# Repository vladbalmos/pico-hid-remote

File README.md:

## HID Bluetooth Remote

HID Bluetooth (BLE) Remote based on a Pico W.

## Hardware requirements

* Pico W
* 5 x micro switches
* TP5100 charging module
* micro USB female
* 1 x 18650 lithium battery (for the V1 enclosure)
* 1 x blackberry q10 lithium battery (for the V2 enclosure)
* 1 x 3mm blue LED + 10k resistor
* 3 x 3mm green LED + 3 x 1k resistors
* 2 x 100k resistors
* pico probe (optional)

## Software dependencies

* pico-sdk (1.5.0)
* pico-extras
* opencd (optional)
* pico probe (optional)

## Build

    make build
    
## Install
Via pico probe:

    make install

## Buttons

* FN
    - long press - turn off
    - double press - show baterry level
    
* PLAY
    - wakeup from sleep if sleeping
    - toggle play/pause
    
* VOL UP
    - increase volume

* VOL DOWN
    - decrease volume

* RESET
    - reset PICO
    
## Behaviour
    
On startup the device is discoverable for one minute, after which, if not paired, the device will go to sleep to preserve battery.

If the device is paired, discoverability is turned off until disconnected.

Once paired, the device will go to sleep if no button press was detected in 10 minutes in order to preserve battery.

### LEDs

* blue
    - flashes while not connected and in pairing mode
    - off once paired
    
* 3 x green
    - show battery level
    - if battery level <= 5% the last led in will flash for 5 seconds

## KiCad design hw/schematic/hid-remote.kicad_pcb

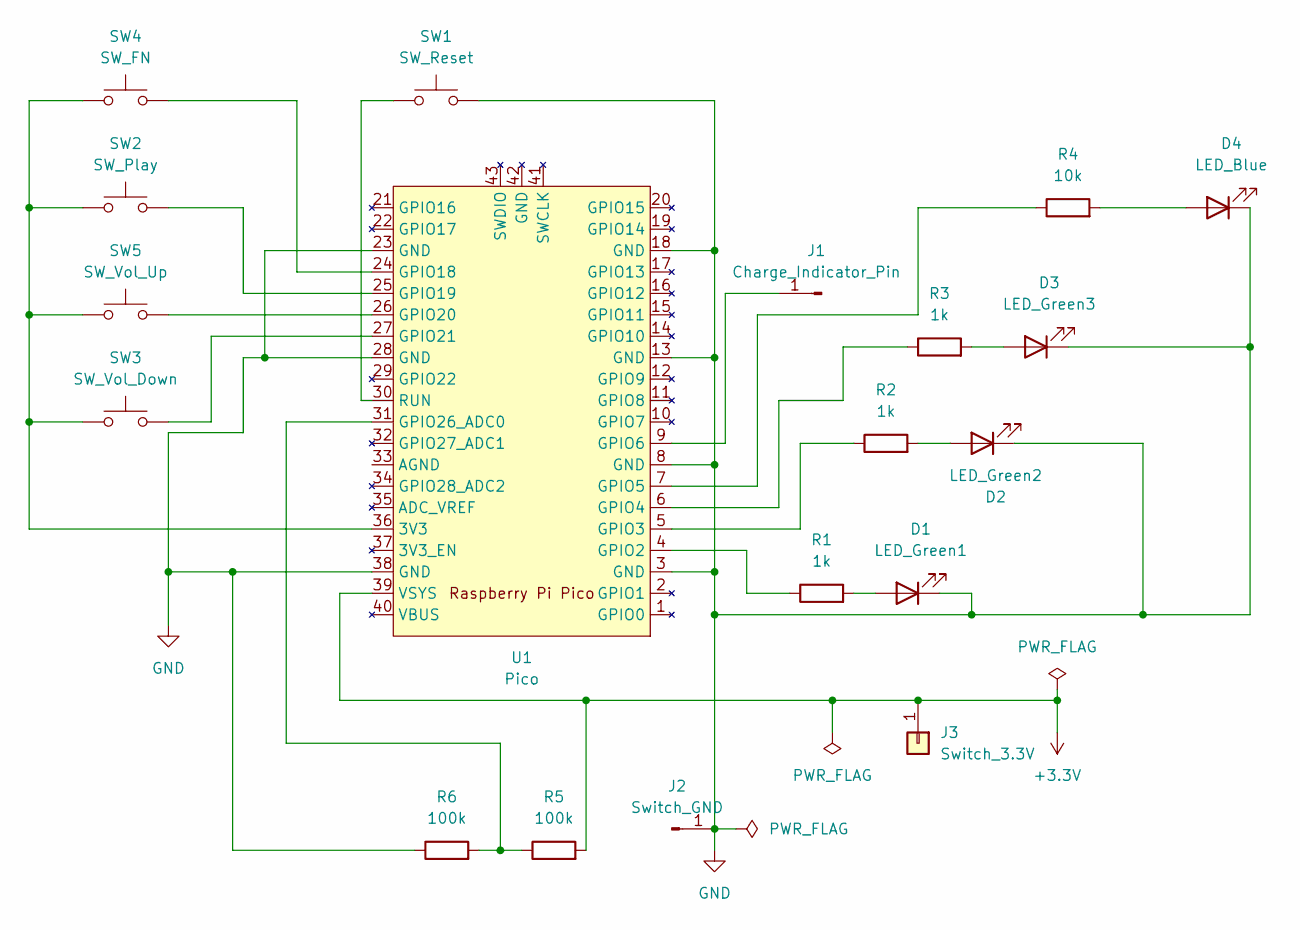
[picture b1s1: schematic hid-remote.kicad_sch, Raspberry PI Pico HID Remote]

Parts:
D1: LED_Green1; LED_0201_0603Metric_Pad0.64x0.40mm_HandSolder
D2: LED_Green2; LED_0201_0603Metric_Pad0.64x0.40mm_HandSolder
D3: LED_Green3; LED_0201_0603Metric_Pad0.64x0.40mm_HandSolder
D4: LED_Blue; LED_0201_0603Metric_Pad0.64x0.40mm_HandSolder
J1: Charge_Indicator_Pin; PinSocket_1x01_P2.54mm_Vertical
J2: Switch_GND; PinSocket_1x01_P2.54mm_Vertical
J3: Switch_3.3V; PinSocket_1x01_P2.54mm_Vertical
R1, R2, R3: 1k; R_Axial_DIN0204_L3.6mm_D1.6mm_P5.08mm_Horizontal
R4: 10k; R_Axial_DIN0207_L6.3mm_D2.5mm_P10.16mm_Horizontal
R5, R6: 100k; R_Axial_DIN0207_L6.3mm_D2.5mm_P10.16mm_Horizontal
SW1: SW_Reset; SW_Push_3x6x5
SW2: SW_Play; SW_Push_3x6x5
SW3: SW_Vol_Down; SW_Push_3x6x5
SW4: SW_FN; SW_Push_3x6x5
SW5: SW_Vol_Up; SW_Push_3x6x5
U1: Pico; RPi_Pico_SMD_TH

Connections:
+3.3V: J3.1, R5.2, U1.39 (VSYS)
GND: D1.1 (K), D2.1 (K), D3.1 (K), D4.1 (K), J2.1, R6.1, SW1.2, U1.3 (GND), U1.8 (GND), U1.13 (GND), U1.18 (GND), U1.23 (GND), U1.28 (GND), U1.38 (GND)
unnamed: D1.2 (A), R1.2
unnamed: D2.2 (A), R2.2
unnamed: D3.2 (A), R3.2
unnamed: D4.2 (A), R4.2
unnamed: J1.1, U1.9 (GPIO6)
unnamed: SW2.1, SW3.1, SW4.1, SW5.1, U1.36 (3V3)
unnamed: R1.1, U1.4 (GPIO2)
unnamed: R2.1, U1.5 (GPIO3)
unnamed: R3.1, U1.6 (GPIO4)
unnamed: R4.1, U1.7 (GPIO5)
unnamed: SW4.2, U1.24 (GPIO18)
unnamed: SW2.2, U1.25 (GPIO19)
unnamed: SW5.2, U1.26 (GPIO20)
unnamed: SW3.2, U1.27 (GPIO21)
unnamed: R5.1, R6.2, U1.31 (GPIO26_ADC0)
unnamed: SW1.1, U1.30 (RUN)

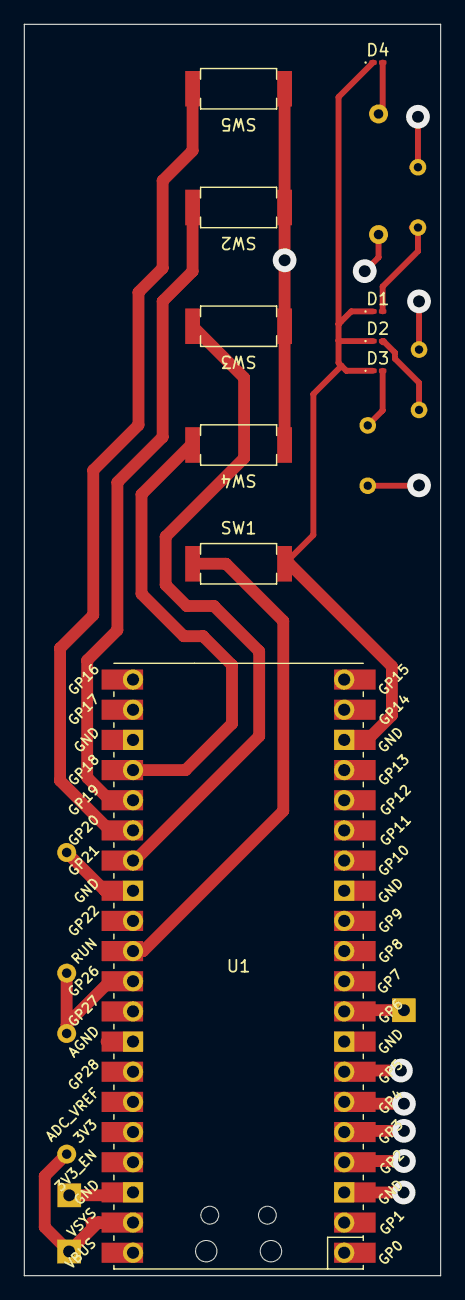
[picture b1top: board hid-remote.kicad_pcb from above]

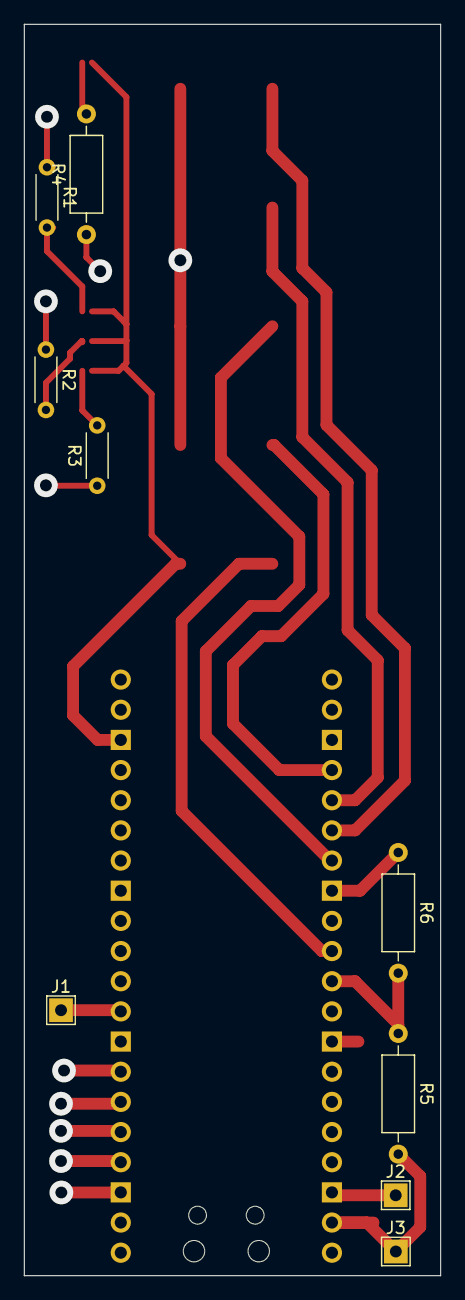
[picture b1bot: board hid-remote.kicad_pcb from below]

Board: 2 copper layers, 35.1 x 105.4 mm, 19 parts (9 on the bottom side), 18 nets.

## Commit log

2023-05-16 Change implementation to BLE HID
2023-05-16 Add LICENSE
2023-05-19 Document Makefile
2023-05-19 Update gitignore
2023-05-19 Refactoring
2023-05-19 Rename gatt header file
2023-05-19 Add battery related logic
2023-05-21 Improvements
2023-05-21 Finish implementing firmware (alpha version)
2023-05-21 Minor fixes
2023-05-21 Add schematic
2023-05-21 Change min / max battery thresholds
2023-05-21 Minor tweaks
2023-05-29 Add case
2023-06-01 Fix comment
2023-06-01 Flash bt connecting led after deep sleep due to input timeout
2023-06-19 Update battery level min threshold
2023-11-11 Add schematic, pcb & case
2023-11-12 Add case descriptions and pictures
2023-11-12 Add cover
